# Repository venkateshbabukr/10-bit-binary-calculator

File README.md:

# 10-bit-binary-calculator
Its just a PCB designed to do 10 bit additions.

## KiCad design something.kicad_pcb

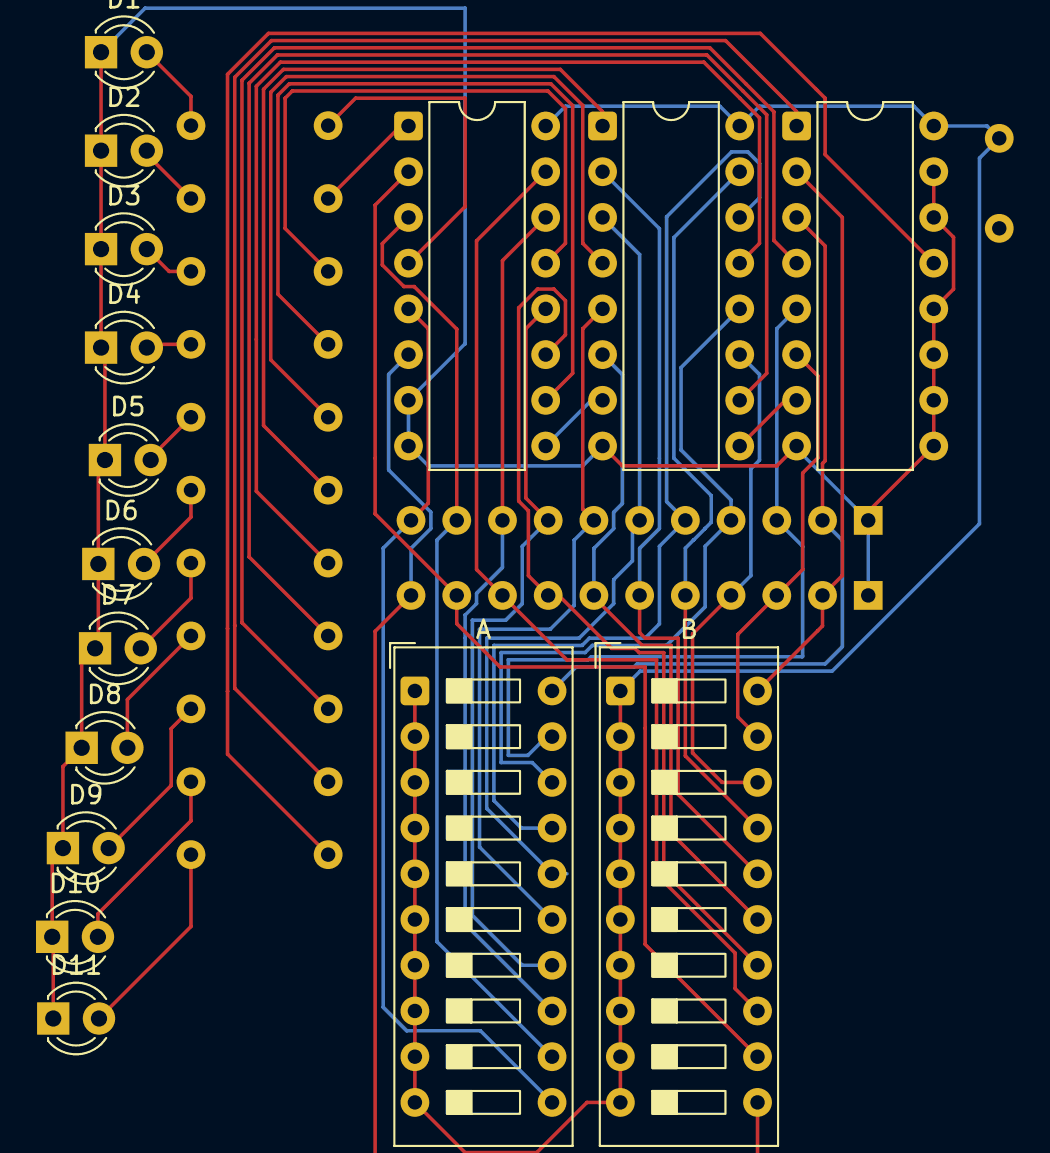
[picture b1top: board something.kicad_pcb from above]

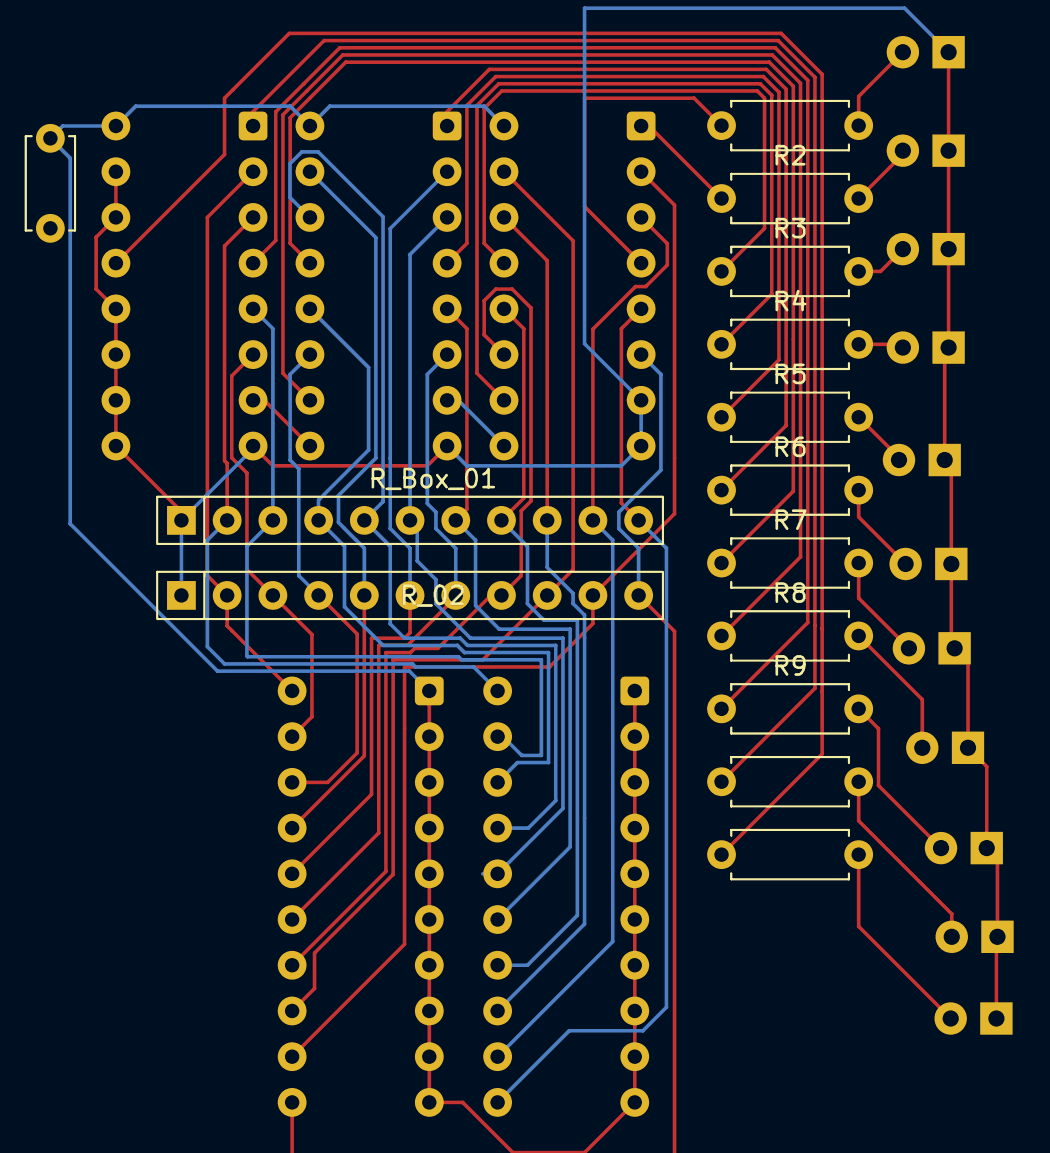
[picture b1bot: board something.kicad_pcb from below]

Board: 2 copper layers, 30 parts (14 on the bottom side), 46 nets.

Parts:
A: SW_DIP_SPSTx10_Slide_9.78x27.58mm_W7.62mm_P2.54mm
B: SW_DIP_SPSTx10_Slide_9.78x27.58mm_W7.62mm_P2.54mm
C1: 100nF; C_Disc_D5.0mm_W2.5mm_P5.00mm
D1, D2, D3, D4, D5, D6, D7, D8, D9, D10, D11: LED_D3.0mm
R1, R2, R3, R4, R5, R6, R7, R8, R9, R10, R11: 220; R_Axial_DIN0207_L6.3mm_D2.5mm_P7.62mm_Horizontal
R_Box_01, R_Box_02: R_Array_SIP11
U1, U2, U3: 74LS283; DIP-16_W7.62mm

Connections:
GND: D1.1 (K), D2.1 (K), D3.1 (K), D4.1 (K), D5.1 (K), D6.1 (K), D7.1 (K), D8.1 (K), D9.1 (K), D10.1 (K), D11.1 (K), R_Box_01.1 (common), R_Box_02.1 (common), U1.7 (C0), U1.8 (GND), U2.8 (GND), U3.8 (GND), U3.9 (C4), U3.10 (S4), U3.11 (B4), U3.12 (A4), U3.14 (A3), U3.15 (B3)
unnamed: D1.2 (A), R1.2
unnamed: D2.2 (A), R2.2
unnamed: D3.2 (A), R3.2
unnamed: D4.2 (A), R4.2
unnamed: D5.2 (A), R5.2
unnamed: D6.2 (A), R6.2
unnamed: D7.2 (A), R7.2
unnamed: D8.2 (A), R8.2
unnamed: D9.2 (A), R9.2
unnamed: D10.2 (A), R10.2
unnamed: D11.2 (A), R11.2
unnamed: A.20, R_Box_01.2 (R1), U3.3 (A2)
unnamed: A.19, R_Box_01.3 (R2), U3.5 (A1)
unnamed: A.18, R_Box_01.4 (R3), U2.12 (A4)
unnamed: A.17, R_Box_01.5 (R4), U2.14 (A3)
unnamed: A.16, R_Box_01.6 (R5), U2.3 (A2)
unnamed: A.15, R_Box_01.7 (R6), U2.5 (A1)
unnamed: A.14, R_Box_01.8 (R7), U1.12 (A4)
unnamed: A.13, R_Box_01.9 (R8), U1.14 (A3)
unnamed: A.12, R_Box_01.10 (R9), U1.3 (A2)
unnamed: A.11, R_Box_01.11 (R10), U1.5 (A1)
unnamed: B.20, R_Box_02.2 (R1), U3.2 (B2)
unnamed: B.19, R_Box_02.3 (R2), U3.6 (B1)
unnamed: B.18, R_Box_02.4 (R3), U2.11 (B4)
unnamed: B.17, R_Box_02.5 (R4), U2.15 (B3)
unnamed: B.16, R_Box_02.6 (R5), U2.2 (B2)
unnamed: B.15, R_Box_02.7 (R6), U2.6 (B1)
unnamed: B.14, R_Box_02.8 (R7), U1.11 (B4)
unnamed: B.13, R_Box_02.9 (R8), U1.15 (B3)
unnamed: B.12, R_Box_02.10 (R9), U1.2 (B2)
unnamed: B.11, R_Box_02.11 (R10), U1.6 (B1)
unnamed: U1.9 (C4), U2.7 (C0)
unnamed: R1.1, U1.4 (S1)
unnamed: R2.1, U1.1 (S2)
unnamed: R3.1, U1.13 (S3)
unnamed: R4.1, U1.10 (S4)
unnamed: A.1, A.2, A.3, A.4, A.5, A.6, A.7, A.8, A.9, A.10, B.1, B.2, B.3, B.4, B.5, B.6, B.7, B.8, B.9, B.10, C1.2, U1.16 (VCC), U2.16 (VCC), U3.16 (VCC)
unnamed: U2.9 (C4), U3.7 (C0)
unnamed: R5.1, U2.4 (S1)
unnamed: R6.1, U2.1 (S2)
unnamed: R7.1, U2.13 (S3)
unnamed: R8.1, U2.10 (S4)
unnamed: R9.1, U3.4 (S1)
unnamed: R10.1, U3.1 (S2)
unnamed: R11.1, U3.13 (S3)
